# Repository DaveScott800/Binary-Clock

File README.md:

# Binary-Clock
A project for Electronics merit badge to build a binary clock.  The hours and minutes are binary coded decimal.  The seconds are ordinary binary (6 leds).  The seconds LEDs only count up once every 5 minutes.
The circuit uses a PIC16F57 and a SN74HC393N.

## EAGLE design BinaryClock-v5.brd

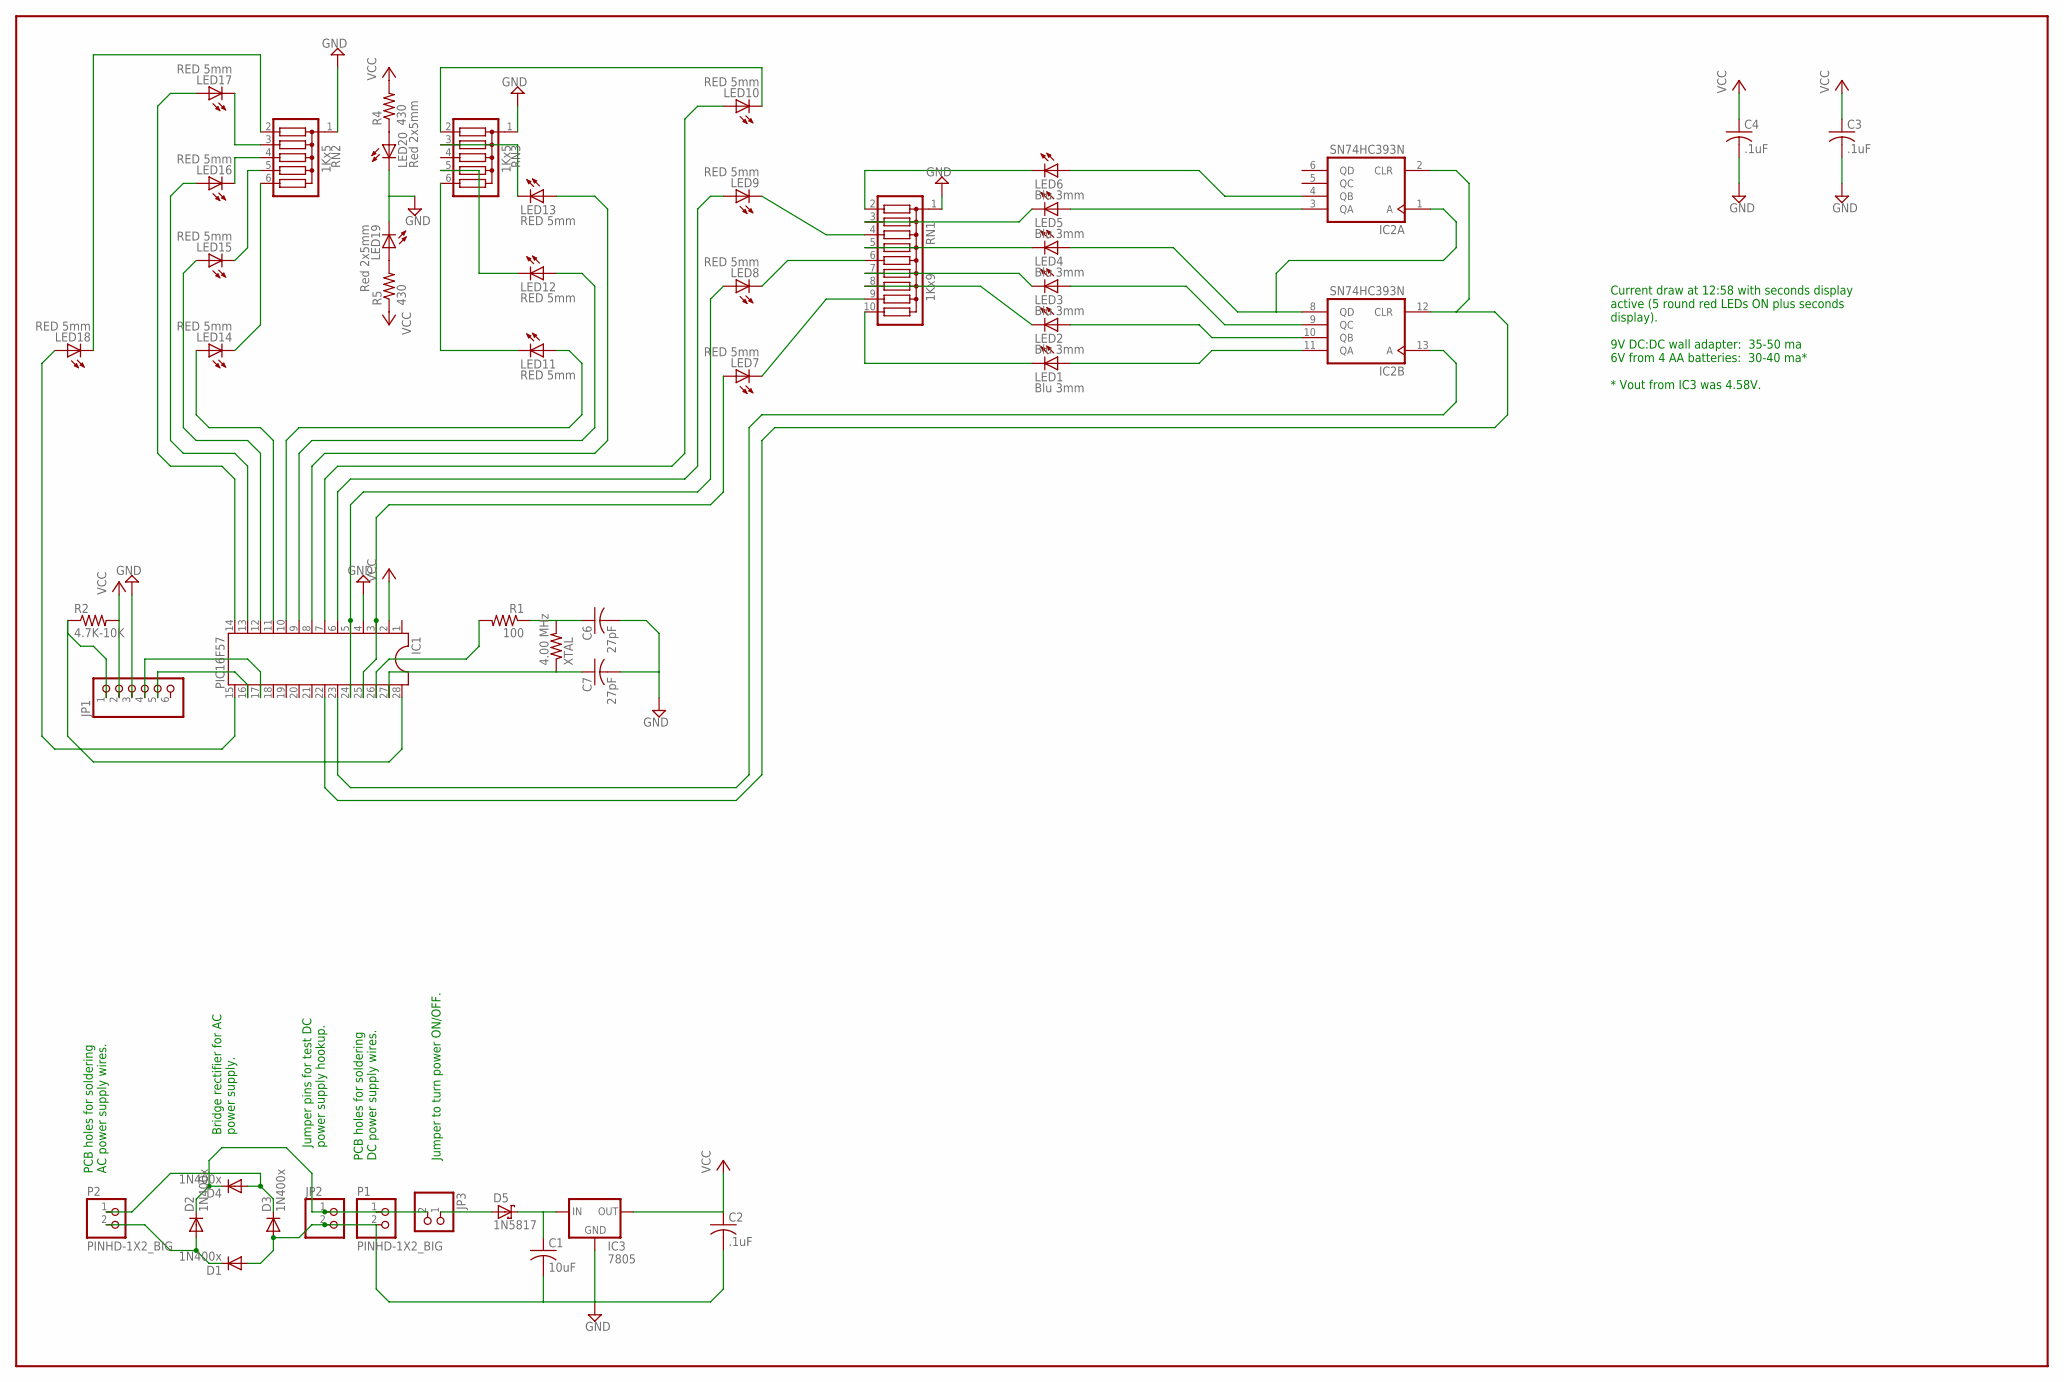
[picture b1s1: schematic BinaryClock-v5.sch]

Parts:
C1: 10uF; C025-050X050
C2, C3, C4: .1uF; C050-025X075
C6, C7: 27pF; C025-025X050
D1, D2, D3, D4: 1N400x; D-7.5
D5: 1N5817; 0207/2V
IC1: PIC16F57; DIL28-3
IC2: SN74HC393N; DIL14
IC3: 7805; 78MXXS
JP1: PINHD-1X6/90; 1X06/90
JP2, JP3: PINHD-1X2; 1X02
LED1, LED2, LED3, LED4, LED5, LED6: Blu 3mm; LED3MM
LED7, LED8, LED9, LED10, LED11, LED12, LED13, LED14, LED15, LED16, LED17, LED18: RED 5mm; LED5MM
LED19, LED20: Red 2x5mm; U57X32
P1, P2: PINHD-1X2_BIG; 1X02_BIG
R1: 100; 0207/7
R2: 4.7K-10K; 0207/2V
R4: 430; 0204/5
R5: 430; 0204/7
RN1: 1Kx9; SIL10
RN2, RN3: 1Kx5; SIL6
XTAL: 4.00 MHz; 0204/5

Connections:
GND: C1.2, C2.2, C3.2, C4.2, C6.2, C7.2, D1.A, D3.A, IC1.4, IC2.7 (GND), IC3.GND, JP1.3, JP2.2, LED19.K (C), LED20.K (C), P1.2, RN1.1, RN2.1, RN3.1
unnamed: IC2.3 (QA), LED5.A
unnamed: IC2.11 (QA), LED1.A
unnamed: IC2.10 (QB), LED2.A
unnamed: IC2.9 (QC), LED3.A
unnamed: IC2.1 (A), IC2.8 (QD), LED4.A
unnamed: C1.1, D5.2 (C), IC3.IN
unnamed: IC2.4 (QB), LED6.A
unnamed: IC1.22, IC2.2 (CLR), IC2.12 (CLR)
unnamed: C7.1, IC1.27, XTAL.1
unnamed: C6.1, R1.1, XTAL.2
unnamed: LED1.K (C), RN1.10
unnamed: IC1.26, R1.2
unnamed: LED7.K (C), RN1.9
unnamed: IC1.28, JP1.1, R2.1
unnamed: IC1.8, LED13.A
unnamed: IC1.16, JP1.5
unnamed: IC1.23, IC2.13 (A)
unnamed: IC1.3, IC1.25, LED7.A
unnamed: IC1.5, IC1.24, LED8.A
unnamed: IC1.6, LED9.A
unnamed: IC1.7, LED10.A
unnamed: IC1.9, LED12.A
unnamed: IC1.10, LED11.A
unnamed: IC1.11, LED14.A
unnamed: IC1.12, LED15.A
unnamed: IC1.13, LED16.A
unnamed: IC1.14, LED17.A
unnamed: IC1.17, JP1.4
unnamed: LED2.K (C), RN1.8
unnamed: LED4.K (C), RN1.5
unnamed: IC1.15, LED18.A
unnamed: LED9.K (C), RN1.4
unnamed: LED3.K (C), RN1.7
unnamed: LED8.K (C), RN1.6
unnamed: LED5.K (C), RN1.3
unnamed: LED6.K (C), RN1.2
unnamed: LED10.K (C), RN3.2
unnamed: LED13.K (C), RN3.3
unnamed: LED11.K (C), RN3.6
unnamed: LED12.K (C), RN3.5
unnamed: LED14.K (C), RN2.6
unnamed: LED15.K (C), RN2.5
unnamed: LED16.K (C), RN2.4
unnamed: LED17.K (C), RN2.3
unnamed: LED18.K (C), RN2.2
unnamed: D2.C, D4.C, JP2.1, JP3.2, P1.1
unnamed: LED20.A, R4.1
unnamed: LED19.A, R5.2
unnamed: D1.C, D2.A, P2.2
unnamed: D3.C, D4.A, P2.1
unnamed: D5.1 (A), JP3.1
VCC: C2.1, C3.1, C4.1, IC1.2, IC2.14 (VCC), IC3.OUT, JP1.2, R2.2, R4.2, R5.1

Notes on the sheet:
PCB holes for soldering AC power supply wires.
Bridge rectifier for AC power supply.
Jumper pins for test DC power supply hookup.
PCB holes for soldering DC power supply wires.
Jumper to turn power ON/OFF.
Current draw at 12:58 with seconds display active (5 round red LEDs ON plus seconds display). 9V DC:DC wall adapter: 35-50 ma 6V from 4 AA batteries: 30-40 ma* * Vout from IC3 was 4.58V.

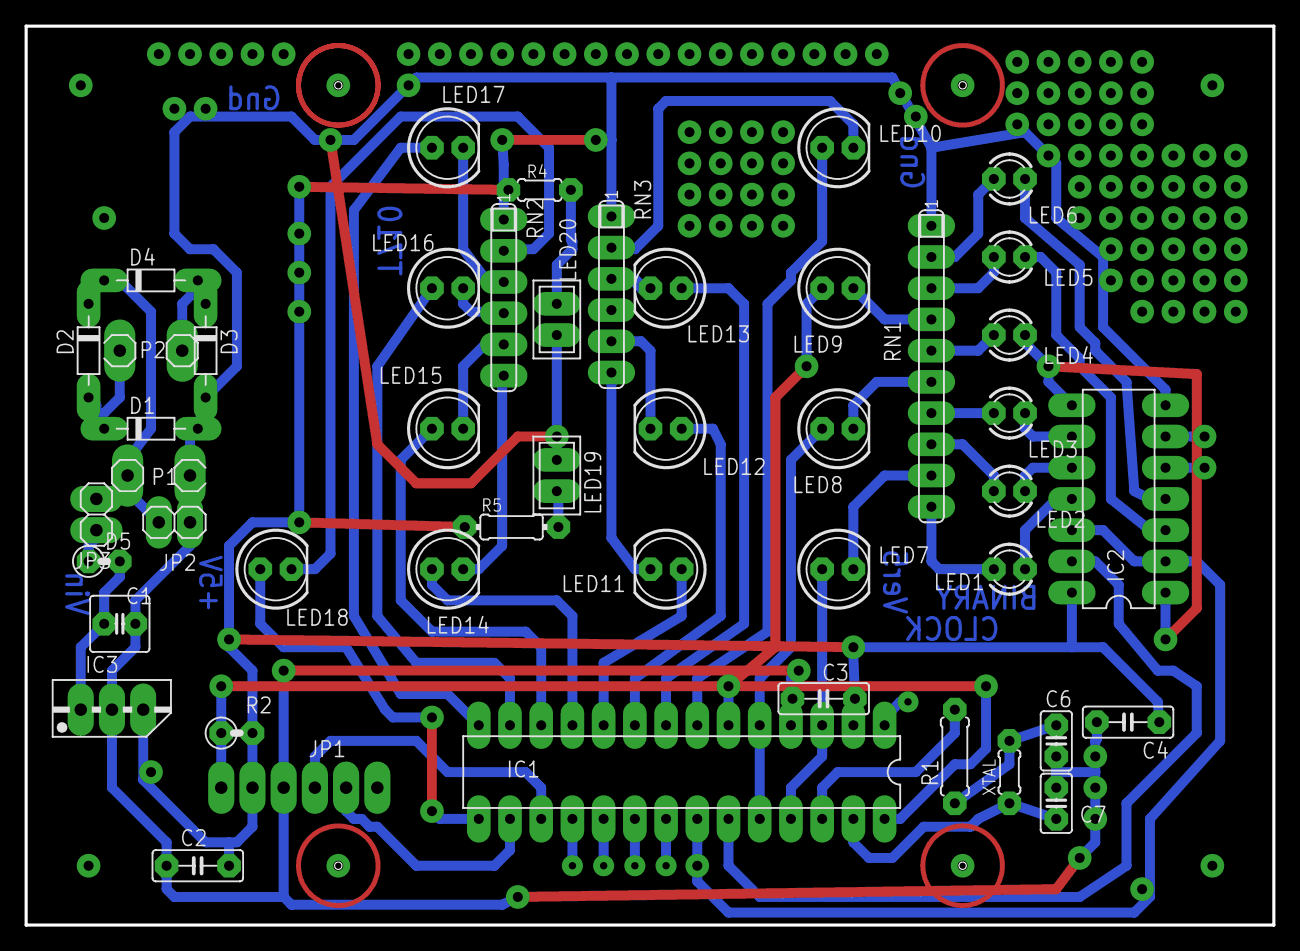
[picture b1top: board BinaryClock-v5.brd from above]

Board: 2 copper layers, 101.5 x 73.1 mm, 47 parts (1 on the bottom side), 53 nets.

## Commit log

2016-07-04 Create Readme.
2016-07-04 Uploaded files.
